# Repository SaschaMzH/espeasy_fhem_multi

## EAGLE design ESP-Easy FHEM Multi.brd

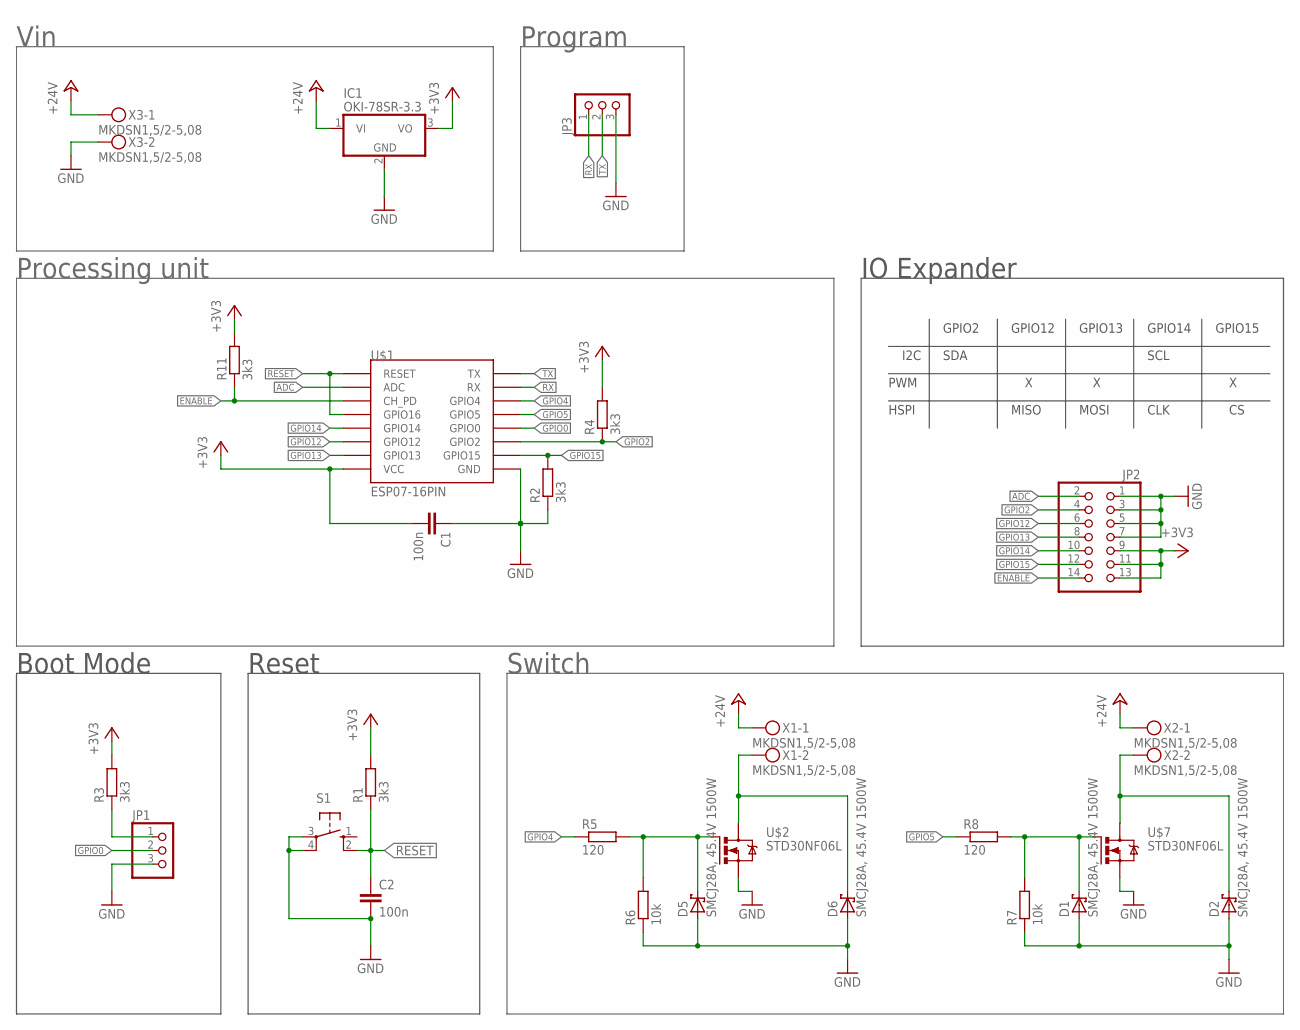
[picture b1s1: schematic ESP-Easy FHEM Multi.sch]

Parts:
C1, C2: 100n; C0603
D1, D2, D5, D6: SMCJ28A, 45.4V 1500W; SMC
IC1: OKI-78SR-3.3; TO220V
JP1, JP3: PINHD-1X3; 1X03
JP2: PINHD-2X7; 2X07
R1, R2, R3, R4, R11: 3k3; R0603
R5, R8: 120; R0603
R6, R7: 10k; R0603
S1: 10-XX; B3F-10XX
U$1: ESP07-16PIN
U$2, U$7: STD30NF06L; D-PAK_TO252AA
X1, X2, X3: MKDSN1,5/2-5,08

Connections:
+3V3: C1.2, IC1.3 (VO), JP2.9, JP2.11, JP2.13, R1.2, R3.2, R4.2, R11.2, U$1.VCC
+24V: IC1.1 (VI), X1.1, X2.1, X3.1
ADC: JP2.2, U$1.ADC
ENABLE: JP2.14, R11.1, U$1.CH_PD
GND: C1.1, C2.2, D1.A, D2.A, D5.A, D6.A, IC1.2 (GND), JP1.3, JP2.1, JP2.3, JP2.5, JP2.7, JP3.3, R2.1, R6.1, R7.1, S1.3, S1.4 (P1), U$1.GND, U$2.3 (S), U$7.3 (S), X3.2
GPIO0: JP1.2, U$1.GPIO0
GPIO2: JP2.4, R4.1, U$1.GPIO2
GPIO4: R5.1, U$1.GPIO4
GPIO5: R8.1, U$1.GPIO5
GPIO12: JP2.6, U$1.GPIO12
GPIO13: JP2.8, U$1.GPIO13
GPIO14: JP2.10, U$1.GPIO14
GPIO15: JP2.12, R2.2, U$1.GPIO15
unnamed: D2.C, U$7.4 (D), X2.2
unnamed: D1.C, R7.2, R8.2, U$7.1 (G)
unnamed: D6.C, U$2.4 (D), X1.2
unnamed: D5.C, R5.2, R6.2, U$2.1 (G)
unnamed: JP1.1, R3.1
RESET: C2.1, R1.1, S1.2 (S1), U$1.GPIO16, U$1.REST (RESET)
RX: JP3.1, U$1.RX
TX: JP3.2, U$1.TX

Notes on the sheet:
Reset
Boot Mode
Vin
Program
GPIO2
GPIO12
GPIO13
GPIO14
GPIO15
I2C
PWM
HSPI
SDA
SCL
MISO
MOSI
CLK
IO Expander
Switch
Processing unit

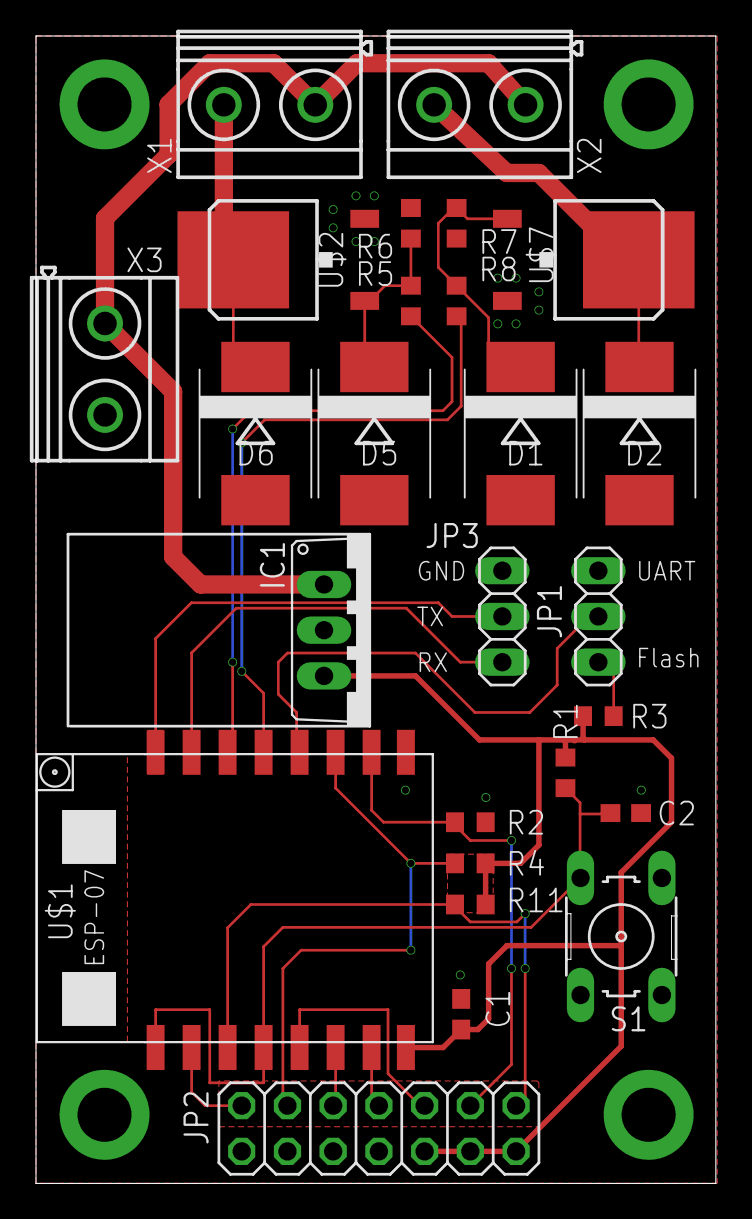
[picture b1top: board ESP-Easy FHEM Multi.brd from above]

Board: 2 copper layers, 37.8 x 63.7 mm, 26 parts (0 on the bottom side), 21 nets.

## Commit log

2017-12-14 Ready to review
2017-12-14 Review Changes
2017-12-14 Last review changes
